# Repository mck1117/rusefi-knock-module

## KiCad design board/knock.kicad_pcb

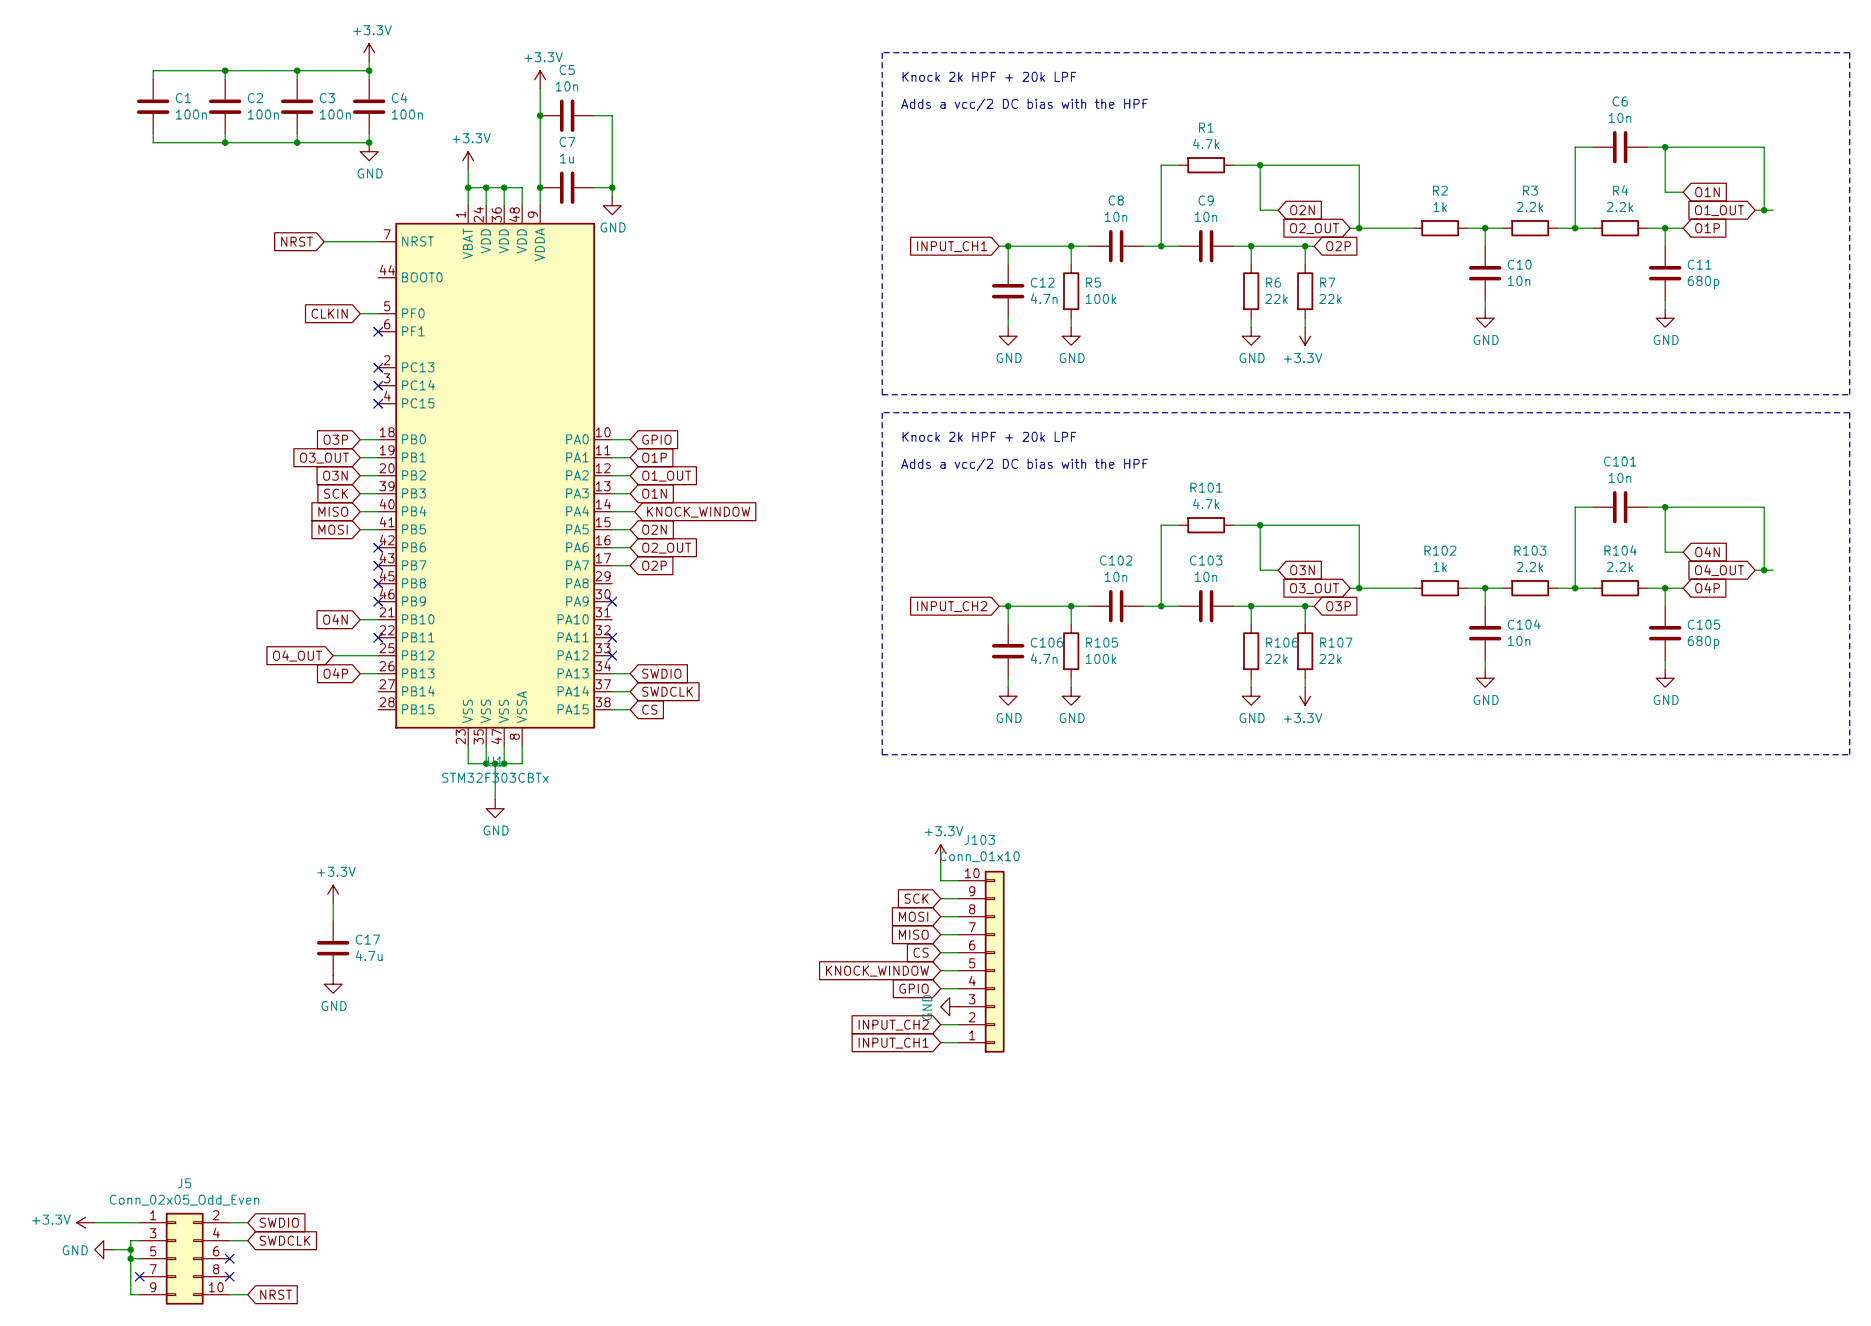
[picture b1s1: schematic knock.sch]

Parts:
C1, C2, C3, C4: 100n; C_0603_1608Metric
C5, C6, C8, C9, C10, C101, C102, C103, C104: 10n; C_0603_1608Metric
C7: 1u; C_0603_1608Metric
C11, C105: 680p; C_0603_1608Metric
C12, C106: 4.7n; C_0603_1608Metric
C17: 4.7u; C_0603_1608Metric
J5: Conn_02x05_Odd_Even; PinHeader_2x05_P1.27mm_Vertical
J103: Conn_01x10; Harwin_M20-89010xx_1x10_P2.54mm_Horizontal
R1, R101: 4.7k; R_0603_1608Metric
R2, R102: 1k; R_0603_1608Metric
R3, R4, R103, R104: 2.2k; R_0603_1608Metric
R5, R105: 100k; R_0603_1608Metric
R6, R7, R106, R107: 22k; R_0603_1608Metric
U1: STM32F303CBTx; LQFP-48_7x7mm_P0.5mm

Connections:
+3V3: C1.1, C2.1, C3.1, C4.1, C5.1, C7.1, C17.1, J5.1, J103.10, R7.2, R107.2, U1.1 (VBAT), U1.9 (VDDA), U1.24 (VDD), U1.36 (VDD), U1.48 (VDD)
CLKIN: U1.5 (PF0)
CS: J103.6, U1.38 (PA15)
GND: C1.2, C2.2, C3.2, C4.2, C5.2, C7.2, C10.1, C11.1, C12.2, C17.2, C104.1, C105.1, C106.2, J5.3, J5.5, J5.9, J103.3, R5.2, R6.2, R105.2, R106.2, U1.8 (VSSA), U1.23 (VSS), U1.35 (VSS), U1.47 (VSS)
GPIO: J103.4, U1.10 (PA0)
INPUT_CH1: C8.2, C12.1, J103.1, R5.1
INPUT_CH2: C102.2, C106.1, J103.2, R105.1
KNOCK_WINDOW: J103.5, U1.14 (PA4)
MISO: J103.7, U1.40 (PB4)
MOSI: J103.8, U1.41 (PB5)
NRST: J5.10, U1.7 (NRST)
unnamed: C6.1, R3.1, R4.2
unnamed: C8.1, C9.2, R1.2
unnamed: C10.2, R2.1, R3.2
unnamed: C101.1, R103.1, R104.2
unnamed: C102.1, C103.2, R101.2
unnamed: C104.2, R102.1, R103.2
O1N: C6.2, U1.12 (PA2), U1.13 (PA3)
O1P: C11.2, R4.1, U1.11 (PA1)
O2N: R1.1, R2.2, U1.15 (PA5), U1.16 (PA6)
O2P: C9.1, R6.1, R7.1, U1.17 (PA7)
O3N: R101.1, R102.2, U1.19 (PB1), U1.20 (PB2)
O3P: C103.1, R106.1, R107.1, U1.18 (PB0)
O4N: C101.2, U1.21 (PB10), U1.25 (PB12)
O4P: C105.2, R104.1, U1.26 (PB13)
SCK: J103.9, U1.39 (PB3)
SWDCLK: J5.4, U1.37 (PA14)
SWDIO: J5.2, U1.34 (PA13)

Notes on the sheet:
Knock 2k HPF + 20k LPF
Adds a vcc/2 DC bias with the HPF

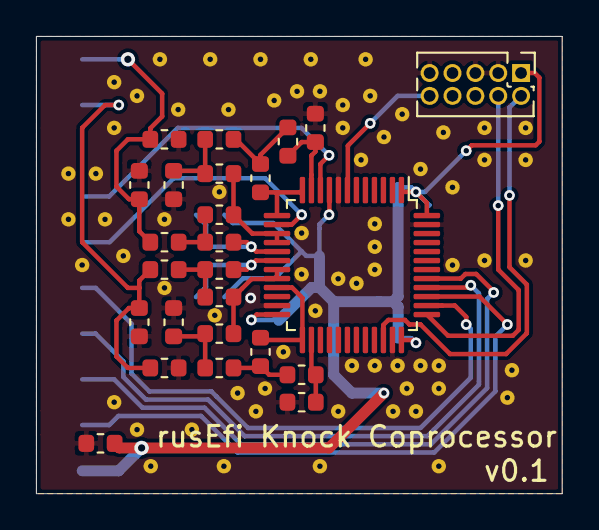
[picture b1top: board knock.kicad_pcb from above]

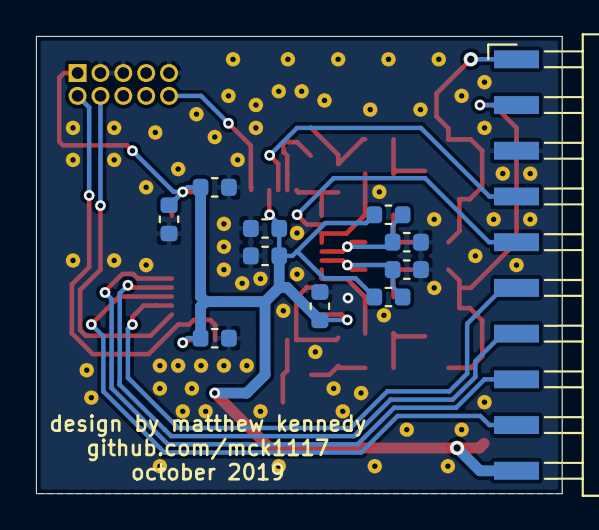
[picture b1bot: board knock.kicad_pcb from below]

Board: 2 copper layers, 29.2 x 25.4 mm, 36 parts (11 on the bottom side), 27 nets.

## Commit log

2020-02-11 ignore mac trash
2020-02-11 add board
2020-02-11 add chibi
2020-02-13 add contrib repo
2020-02-13 ignore more
2020-02-13 add fw stub
2020-02-13 casing
2020-02-13 modules fix maybe
2020-02-13 fix modules maybe
2020-02-13 bluh
2020-02-15 switch to hsi
2020-02-15 add board config
2020-02-15 init properly
2020-02-15 remove submodule
2020-02-15 add adc
2020-02-15 conf
2020-02-15 clock & adc config
2020-02-15 adc works
2020-02-15 didn't need that
